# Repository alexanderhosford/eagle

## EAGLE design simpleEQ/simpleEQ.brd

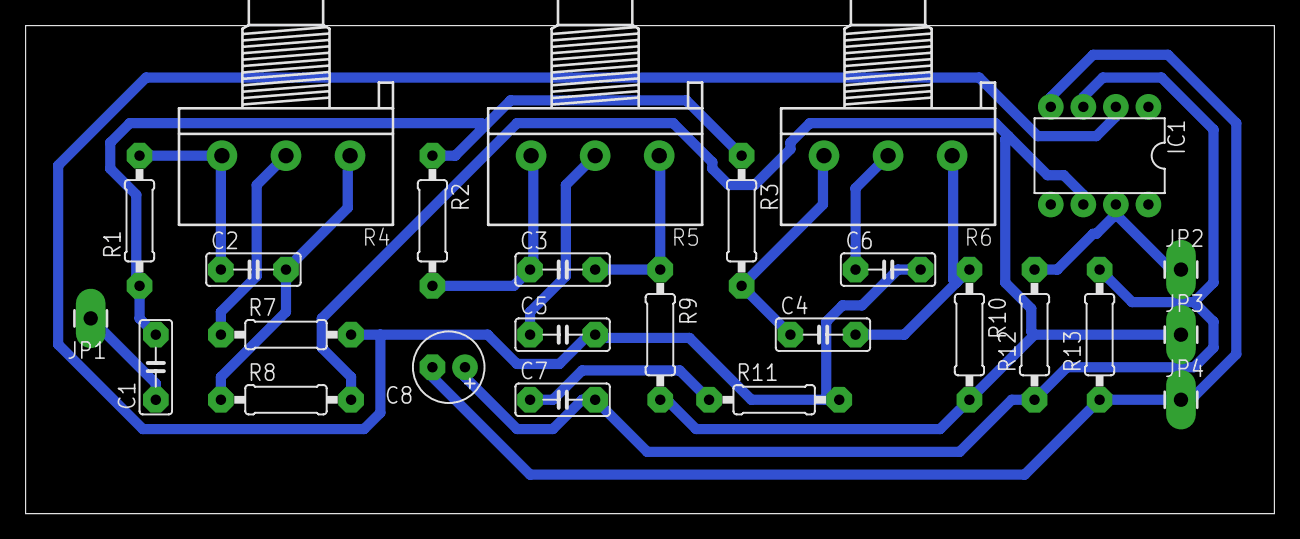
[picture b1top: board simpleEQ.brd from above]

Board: 2 copper layers, 97.5 x 38.1 mm, 26 parts (0 on the bottom side), 17 nets.

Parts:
C1: 0.1µ; C050-025X075
C2: 47n; C050-025X075
C3, C6: 4n7; C050-025X075
C4: n47; C050-025X075
C5: 22n; C050-025X075
C7: 1n; C050-025X075
C8: 33µ; E2,5-6
IC1: TL071P; DIL08
JP1: INPUT; 1X01_LONGPAD
JP2: +12V; 1X01_LONGPAD
JP3: OUTPUT; 1X01_LONGPAD
JP4: GND; 1X01_LONGPAD
R1, R7, R8, R12, R13: 10k; 0207/10
R2, R9: 3k3; 0207/10
R3, R10: 1k8; 0207/10
R4, R5: 100k; 3RP/1610N
R6: 470k; 3RP/1610N
R11: 270R; 0207/10

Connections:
GND: C8.-, IC1.4, JP4.1, R13.1
unnamed: IC1.7, JP2.1, R12.2
unnamed: C5.1, R5.2
unnamed: C3.1, R2.2, R5.3
unnamed: C7.2, C8.+, IC1.3, R12.1, R13.2
unnamed: C3.2, R5.1, R9.1
unnamed: C7.1, R11.1
unnamed: C5.2, C6.2, IC1.2, R7.2, R11.2
unnamed: R4.2, R7.1
unnamed: C2.2, R4.1, R8.1
unnamed: C2.1, R1.2, R4.3
unnamed: C6.1, R6.2
unnamed: C4.1, R3.2, R6.3
unnamed: C4.2, R6.1, R10.1
unnamed: IC1.6, JP3.1, R8.2, R9.2, R10.2
unnamed: C1.2, R1.1, R2.1, R3.1
unnamed: C1.1, JP1.1

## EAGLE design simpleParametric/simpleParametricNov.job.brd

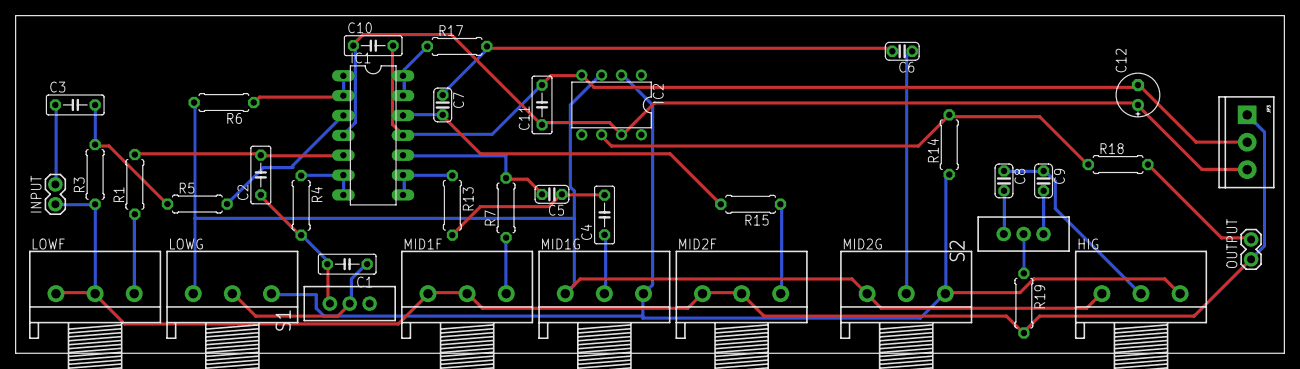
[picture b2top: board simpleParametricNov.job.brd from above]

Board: 2 copper layers, 162.2 x 43.2 mm, 38 parts (0 on the bottom side), 30 nets.

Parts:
C1, C3: 1Âµ; C050-025X075
C2: 47n; C050-025X075
C4: 150n; C050-025X075
C5, C6, C8: 22n; C025-024X044
C7, C9: 10n; C025-024X044
C10, C11: 100n; C050-025X075
C12: 10Âµ; E2,5-6E
HIG: 10k; 3RP/1610N
IC1: TL074; DIL14
IC2: NE5534N; DIL08
INPUT: 1X02
JP3: POWER; SCREWTERMINAL-3.5MM-3
LOWF: 1M; 3RP/1610N
LOWG: 10k; 3RP/1610N
MID1F, MID2F: 1M; 3RP/1610N
MID1G, MID2G: 10k; 3RP/1610N
OUTPUT: 1X02
R1, R7, R15: 47k; 0207/7
R3: 100k; 0207/7
R4, R13, R17, R19: 470R; 0207/7
R5: 1k; 0207/7
R6, R14: 2k7; 0207/7
R18: 100R; 0207/7
S1: Shelf / Peak; SWITCH-SPDT
S2: 2.5kHz / 5kHz; SWITCH-SPDT

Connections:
GND: INPUT.1, JP3.1, LOWF.1, LOWF.2, MID1F.1, MID1F.2, MID2F.1, MID2F.2, OUTPUT.1, R3.1, R19.2
unnamed: C1.2, C2.1, R4.2, S1.1
unnamed: C4.2, C5.1, R13.2
unnamed: C6.2, C7.1, R17.2
unnamed: C9.2, S2.3
unnamed: C8.2, S2.1
unnamed: R19.1, S2.2
unnamed: IC1.13, IC1.14, R17.1
unnamed: C7.2, IC1.12, R15.2
unnamed: MID2F.3, R15.1
unnamed: C3.1, INPUT.2
unnamed: C3.2, R3.2, R5.1
unnamed: IC1.3, R5.2
unnamed: IC1.1, IC1.2, R6.1
unnamed: HIG.1, IC2.3, LOWG.1, MID1G.1, MID2G.1, R6.2
unnamed: IC2.6, R14.2, R18.1
unnamed: OUTPUT.2, R18.2
unnamed: HIG.3, IC2.2, LOWG.3, MID1G.3, MID2G.3, R14.1
unnamed: IC1.6, IC1.7, R4.1
unnamed: C2.2, IC1.5, R1.2
unnamed: LOWF.3, R1.1
unnamed: C1.1, LOWG.2, S1.2
unnamed: IC1.8, IC1.9, R13.1
unnamed: C5.2, IC1.10, R7.2
unnamed: MID1F.3, R7.1
unnamed: C6.1, MID2G.2
unnamed: C8.1, C9.1, HIG.2
V+: C10.1, C11.1, C12.+, IC1.4, IC2.7, JP3.3
V-: C10.2, C11.2, C12.-, IC1.11, IC2.4, JP3.2
VIA1: C4.1, MID1G.2

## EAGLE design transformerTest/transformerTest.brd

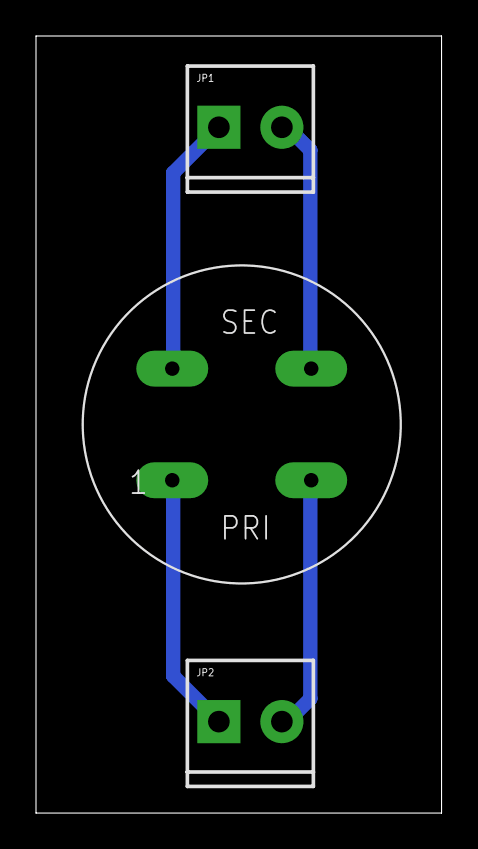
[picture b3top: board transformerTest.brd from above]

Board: 2 copper layers, 22.5 x 43.2 mm, 3 parts (0 on the bottom side), 4 nets.

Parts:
JP1, JP2: SCREWTERMINAL-3.5MM-2
T1: 855-INPUT-TRANSFORMER

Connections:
unnamed: JP2.1, T1.P$1
unnamed: JP2.2, T1.P$2
unnamed: JP1.1, T1.P$3
unnamed: JP1.2, T1.P$4

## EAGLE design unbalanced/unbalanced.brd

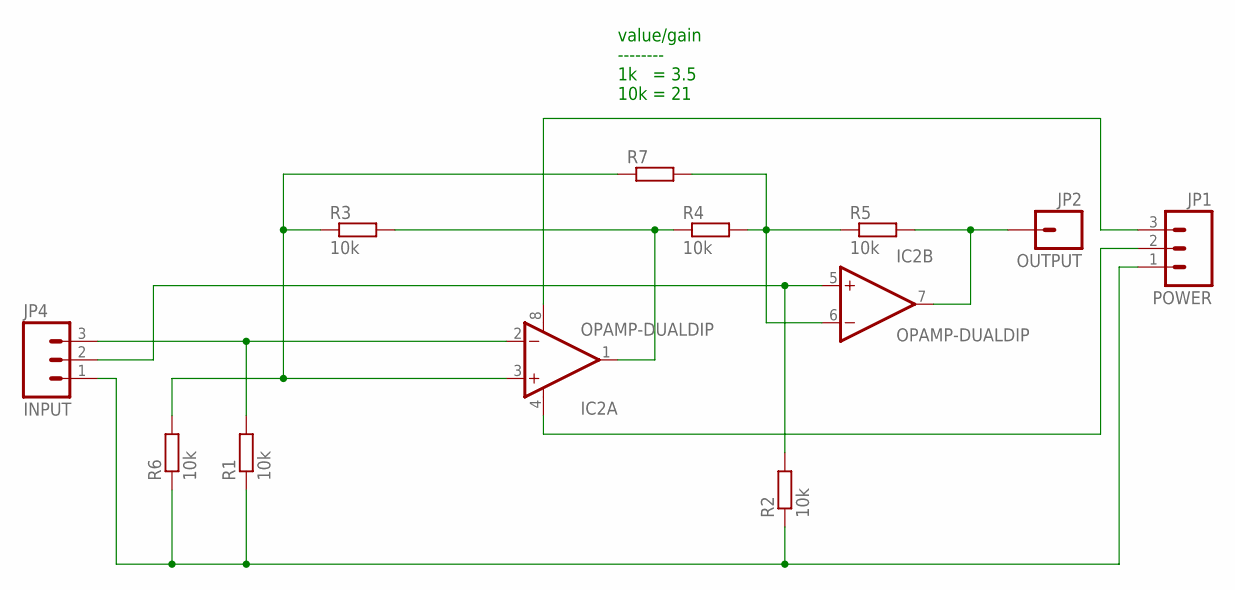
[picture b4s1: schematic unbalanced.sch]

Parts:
IC2: OPAMP-DUALDIP; DIP08
JP1: POWER; SCREWTERMINAL-3.5MM-3
JP2: OUTPUT; 1X01
JP4: INPUT; SCREWTERMINAL-3.5MM-3
R1, R2, R3, R4, R5, R6: 10k; 0207/10
R7: R-EU_0207/10; 0207/10

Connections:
unnamed: IC2.7 (OUT), JP2.1, R5.2
unnamed: IC2.6 (-IN), R4.2, R5.1, R7.2
unnamed: IC2.1 (OUT), R3.2, R4.1
unnamed: IC2.2 (-IN), JP4.3, R1.2
unnamed: IC2.3 (+IN), R3.1, R6.2, R7.1
unnamed: IC2.8 (V+), JP1.3
unnamed: IC2.4 (V-), JP1.2
unnamed: JP1.1, JP4.1, R1.1, R2.1, R6.1
unnamed: IC2.5 (+IN), JP4.2, R2.2

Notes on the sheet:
value/gain -------- 1k = 3.5 10k = 21

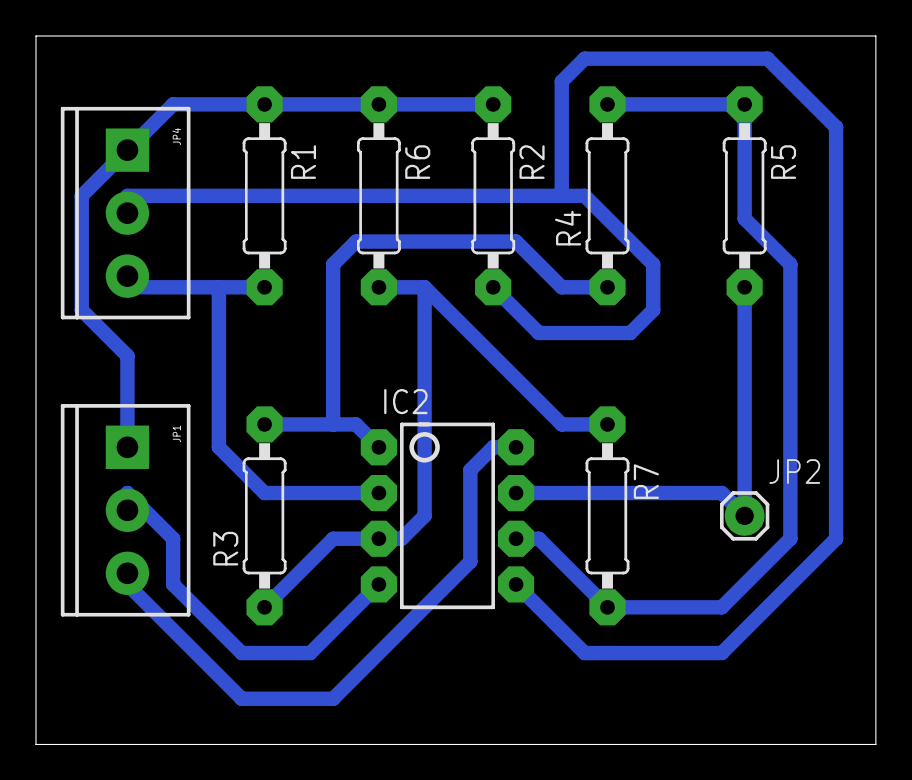
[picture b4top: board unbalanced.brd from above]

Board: 2 copper layers, 46.7 x 39.4 mm, 11 parts (0 on the bottom side), 9 nets.

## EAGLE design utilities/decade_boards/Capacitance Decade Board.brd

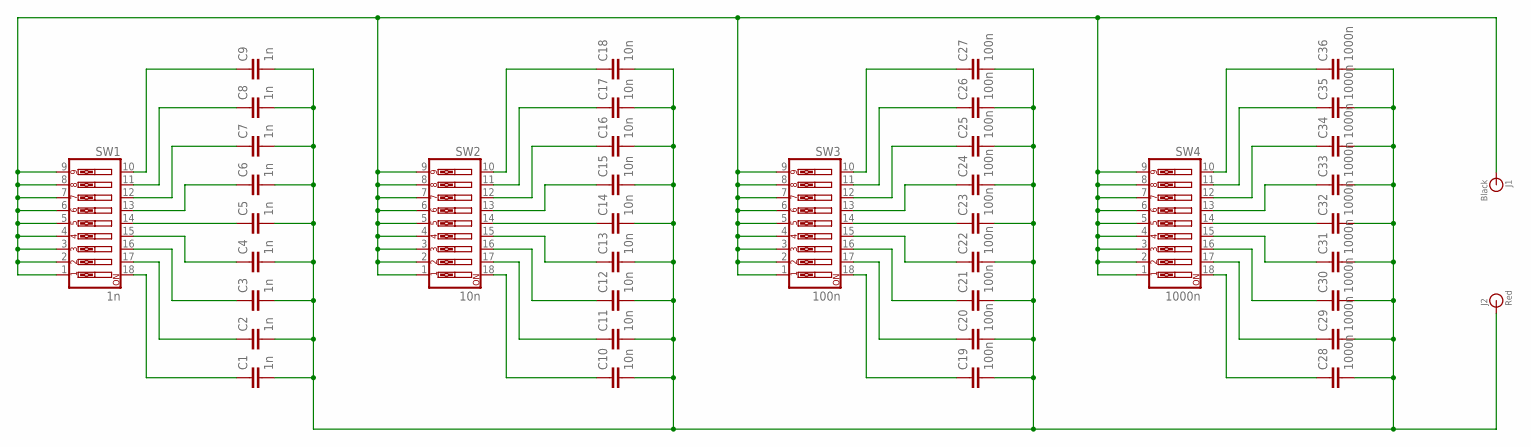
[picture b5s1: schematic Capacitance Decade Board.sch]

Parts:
C1, C2, C3, C4, C5, C6, C7, C8, C9: 1n; C050-024X044
C10, C11, C12, C13, C14, C15, C16, C17, C18: 10n; C050-024X044
C19, C20, C21, C22, C23, C24, C25, C26, C27: 100n; C050-024X044
C28, C29, C30, C31, C32, C33, C34, C35, C36: 1000n; C050-024X044
J1: Black; BANANA_CONN
J2: Red; BANANA_CONN
SW1: 1n; EDG-09
SW2: 10n; EDG-09
SW3: 100n; EDG-09
SW4: 1000n; EDG-09

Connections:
unnamed: C1.1, SW1.18
unnamed: C2.1, SW1.17
unnamed: C3.1, SW1.16
unnamed: C9.1, SW1.10
unnamed: C8.1, SW1.11
unnamed: C7.1, SW1.12
unnamed: C4.1, SW1.15
unnamed: C5.1, SW1.14
unnamed: C6.1, SW1.13
unnamed: C10.1, SW2.18
unnamed: C11.1, SW2.17
unnamed: C12.1, SW2.16
unnamed: C18.1, SW2.10
unnamed: C17.1, SW2.11
unnamed: C16.1, SW2.12
unnamed: C13.1, SW2.15
unnamed: C14.1, SW2.14
unnamed: C15.1, SW2.13
unnamed: C19.1, SW3.18
unnamed: C20.1, SW3.17
unnamed: C21.1, SW3.16
unnamed: C27.1, SW3.10
unnamed: C26.1, SW3.11
unnamed: C25.1, SW3.12
unnamed: C22.1, SW3.15
unnamed: C23.1, SW3.14
unnamed: C24.1, SW3.13
unnamed: C28.1, SW4.18
unnamed: C29.1, SW4.17
unnamed: C30.1, SW4.16
unnamed: C36.1, SW4.10
unnamed: C35.1, SW4.11
unnamed: C34.1, SW4.12
unnamed: C31.1, SW4.15
unnamed: C32.1, SW4.14
unnamed: C33.1, SW4.13
unnamed: C1.2, C2.2, C3.2, C4.2, C5.2, C6.2, C7.2, C8.2, C9.2, C10.2, C11.2, C12.2, C13.2, C14.2, C15.2, C16.2, C17.2, C18.2, C19.2, C20.2, C21.2, C22.2, C23.2, C24.2, C25.2, C26.2, C27.2, C28.2, C29.2, C30.2, C31.2, C32.2, C33.2, C34.2, C35.2, C36.2, J2.P$1
unnamed: J1.P$1, SW1.1, SW1.2, SW1.3, SW1.4, SW1.5, SW1.6, SW1.7, SW1.8, SW1.9, SW2.1, SW2.2, SW2.3, SW2.4, SW2.5, SW2.6, SW2.7, SW2.8, SW2.9, SW3.1, SW3.2, SW3.3, SW3.4, SW3.5, SW3.6, SW3.7, SW3.8, SW3.9, SW4.1, SW4.2, SW4.3, SW4.4, SW4.5, SW4.6, SW4.7, SW4.8, SW4.9

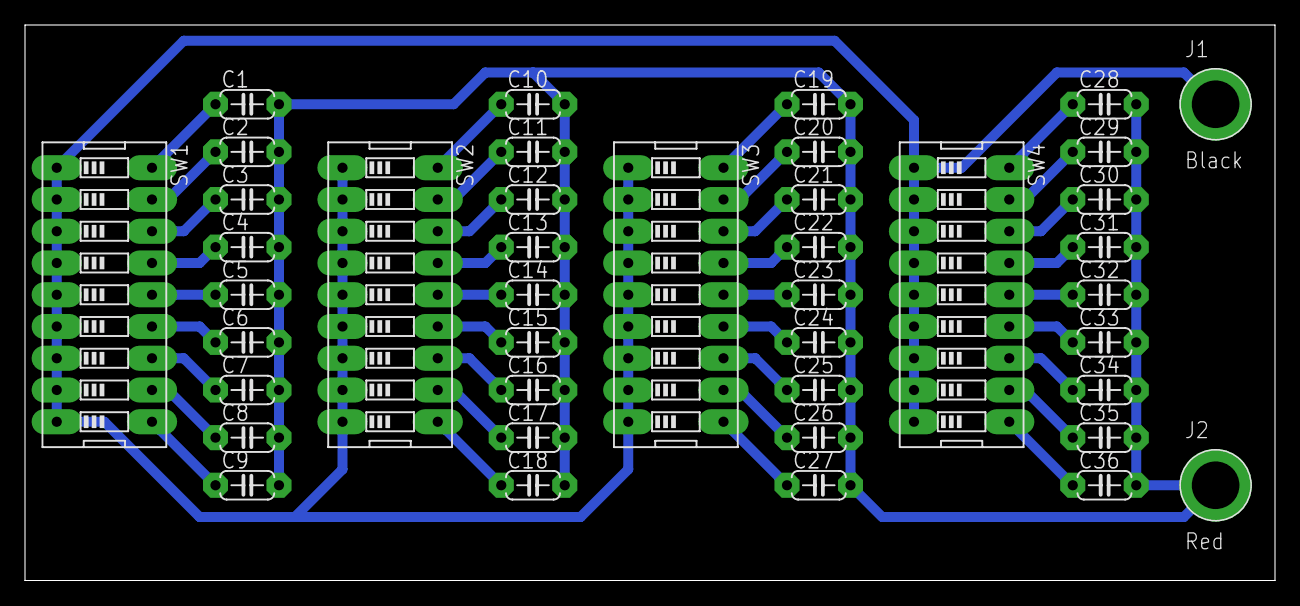
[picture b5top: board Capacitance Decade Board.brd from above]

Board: 2 copper layers, 100.0 x 44.4 mm, 42 parts (0 on the bottom side), 38 nets.

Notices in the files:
parts and their libraries:
SparkFun: Licensing: CC v3.0 Share-Alike You are welcome to use this library for commercial purposes.
